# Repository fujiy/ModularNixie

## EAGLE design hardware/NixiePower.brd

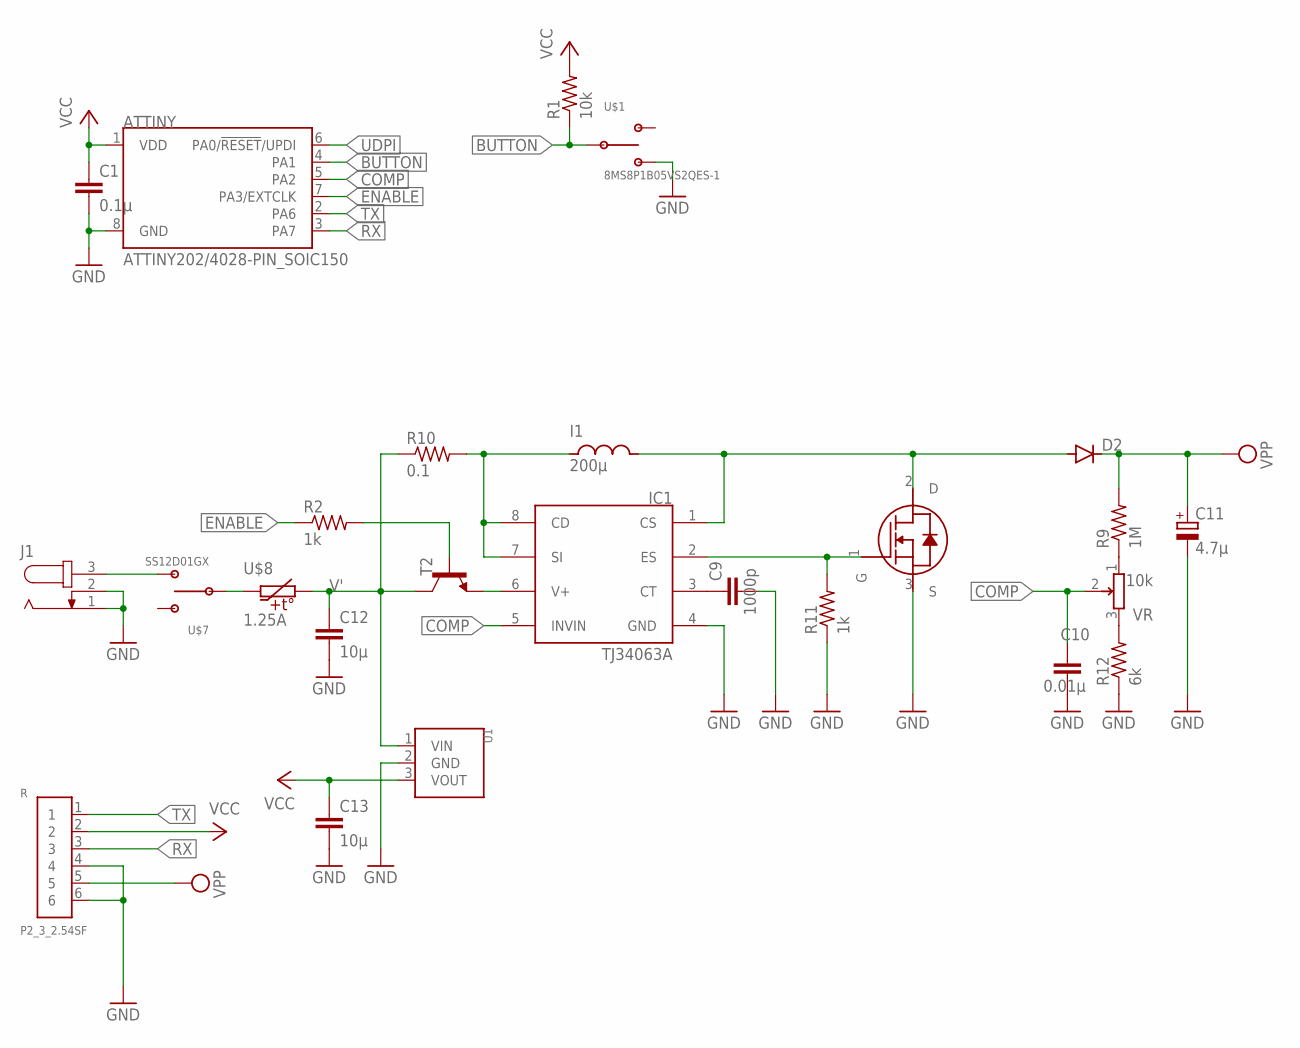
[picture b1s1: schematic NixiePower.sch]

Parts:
ATTINY: ATTINY202/4028-PIN_SOIC150; SOIC127P600X175-8N
C1: 0.1µ; C0603
C9: 1000p; C0603
C10: 0.01µ; C0603
C11: 4.7µ; E5-10,5
C12, C13: 10µ; C0603
D2: DIODE-DO15-12; DO15-12
I1: 200µ; NR10050
IC1: TJ34063A; SOP8
J1: JACK-PLUG1; SPC4078
R: P2_3_2.54SF
R1: 10k; R0603
R2, R11: 1k; R0603
R9: 1M; R0603
R10: 0.1; R0603
R12: 6k; R0603
T1: R6006AND; CPT3
T2: -NPN-SOT23-EBC; SOT23-EBC
U1: VX078XX-500
U$1: 8MS8P1B05VS2QES-1
U$7: SS12D01GX
U$8: 1.25A; SMD1812P
VR: 10k; RK09D

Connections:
BUTTON: ATTINY.4 (PA1), R1.1, U$1.2 (C)
COMP: ATTINY.5 (PA2), C10.1, IC1.5 (INVIN), VR.2
ENABLE: ATTINY.7 (PA3/EXTCLK), R2.1
GND: ATTINY.8 (GND), C1.2, C9.2, C10.2, C11.-, C12.2, C13.2, IC1.4 (GND), J1.1, J1.2, R.4, R.6, R11.1, R12.1, T1.3 (S), U1.2 (GND), U$1.3 (B)
unnamed: IC1.6 (V+), T2.E
unnamed: R2.2, T2.B
unnamed: U$7.2 (C), U$8.1
unnamed: J1.3, U$7.3 (B)
unnamed: D2.A, I1.2, IC1.1 (CS), T1.2 (D)
unnamed: C9.1, IC1.3 (CT)
unnamed: I1.1, IC1.7 (SI), IC1.8 (CD), R10.2
unnamed: IC1.2 (ES), R11.2, T1.1 (G)
unnamed: R9.1, VR.1 (3)
unnamed: R12.2, VR.3 (1)
RX: ATTINY.3 (PA7), R.3
TX: ATTINY.2 (PA6), R.1
UDPI: ATTINY.6 (PA0/!RESET!/UPDI)
V': C12.1, R10.1, T2.C, U1.1 (VIN), U$8.2
VCC: ATTINY.1 (VDD), C1.1, C13.1, R.2, R1.2, U1.3 (VOUT)
VPP: C11.+, D2.C, R.5, R9.2

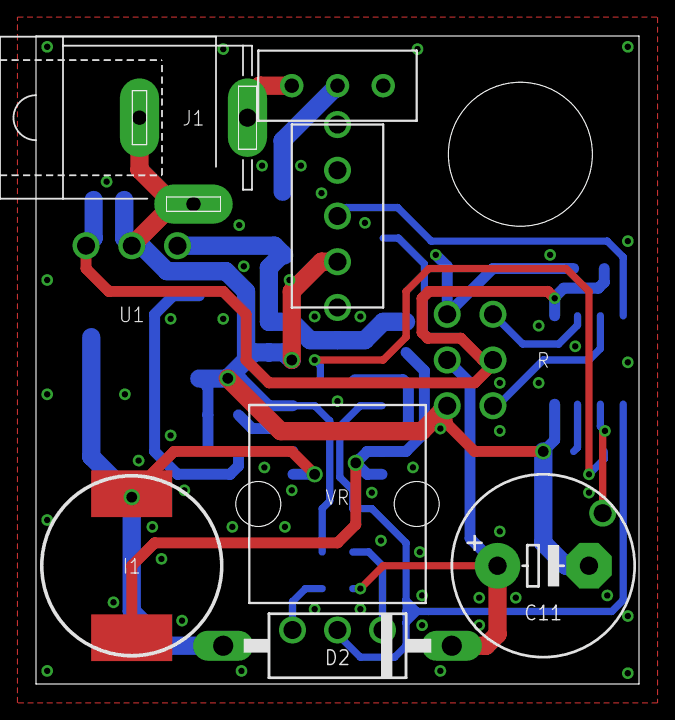
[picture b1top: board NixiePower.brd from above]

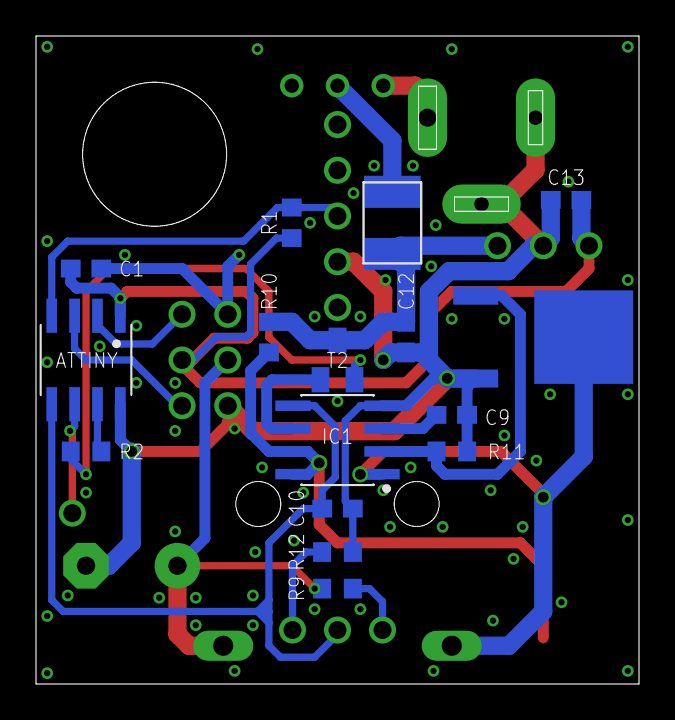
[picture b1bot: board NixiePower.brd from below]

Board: 2 copper layers, 33.5 x 36.0 mm, 25 parts (16 on the bottom side), 19 nets.

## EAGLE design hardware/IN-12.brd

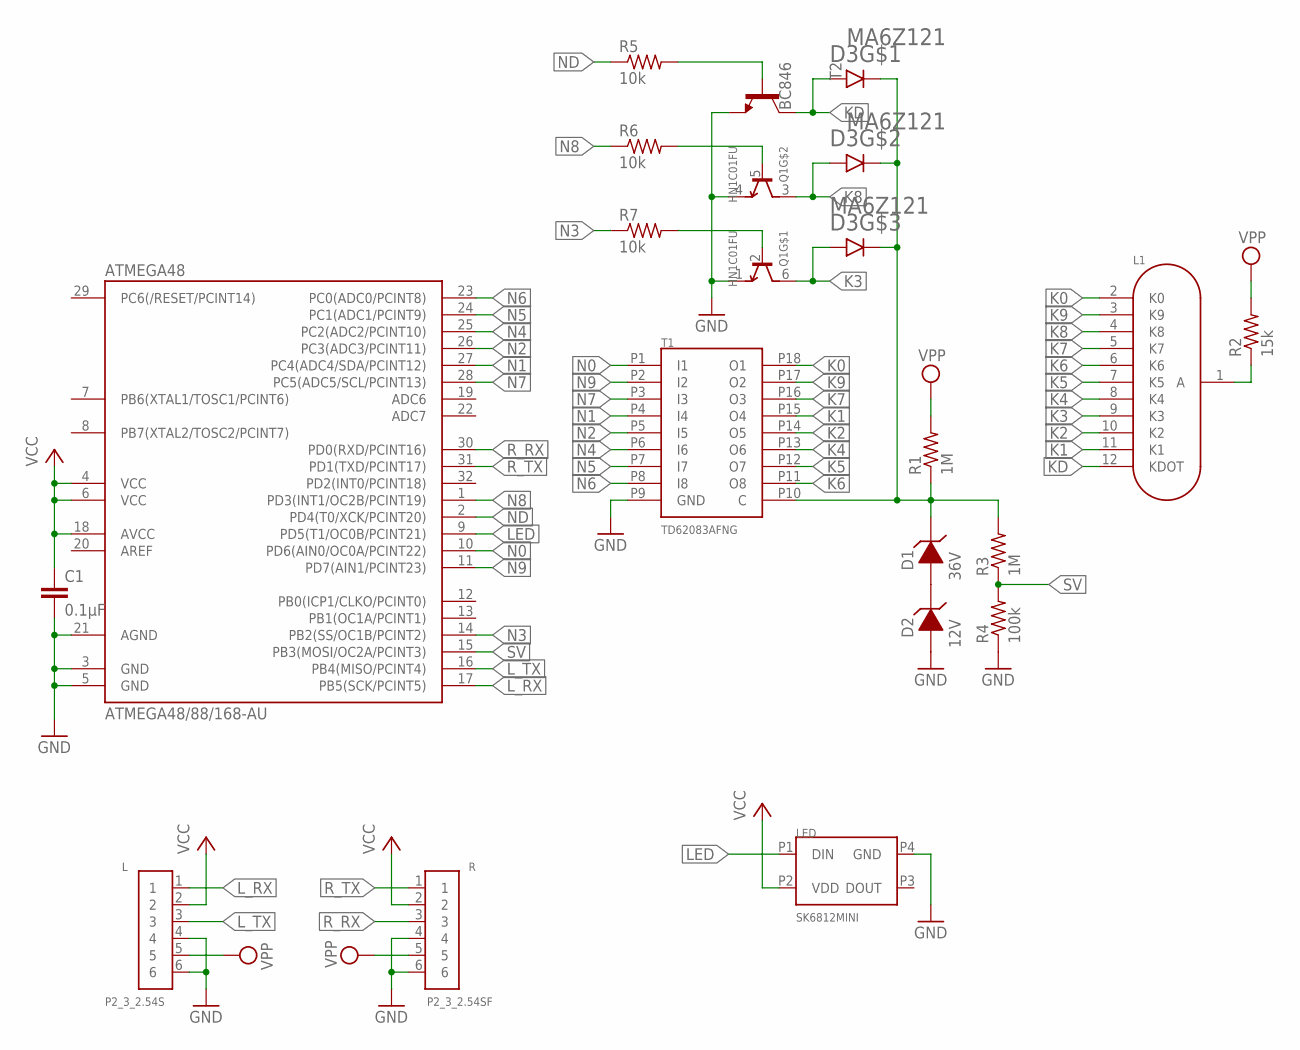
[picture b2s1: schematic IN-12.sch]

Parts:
ATMEGA48: ATMEGA48/88/168-AU; TQFP32-08
C1: 0.1µF; C0603
D1: 36V; S-MINI-2P
D2: 12V; S-MINI-2P
D3: MA6Z121; SMINI6-F1
L: P2_3_2.54S
L1: IN-12B_PS; IN-12_PS
LED: SK6812MINI; SK68XXMINI
Q1: HN1C01FU; SOT-363
R: P2_3_2.54SF
R1, R3: 1M; R0603
R2: 15k; R1206
R4: 100k; R0603
R5, R6, R7: 10k; R0603
T1: TD62083AFNG; SSOP18-P-225-0.65
T2: BC846; SOT23

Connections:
GND: ATMEGA48.3 (GND), ATMEGA48.5 (GND), ATMEGA48.21 (AGND), C1.2, D2.1 (A), L.4, L.6, LED.P4 (GND), Q1.1 (E), Q1.4 (E), R.4, R.6, R4.1, T1.P9 (GND), T2.2 (E)
K0: L1.2 (K0), T1.P18 (O1)
K1: L1.11 (K1), T1.P15 (O4)
K2: L1.10 (K2), T1.P14 (O5)
K3: D3.P3 (A), L1.9 (K3), Q1.6 (C)
K4: L1.8 (K4), T1.P13 (O6)
K5: L1.7 (K5), T1.P12 (O7)
K6: L1.6 (K6), T1.P11 (O8)
K7: L1.5 (K7), T1.P16 (O3)
K8: D3.P2 (A), L1.4 (K8), Q1.3 (C)
K9: L1.3 (K9), T1.P17 (O2)
KD: D3.P1 (A), L1.12 (KDOT), T2.3 (C)
LED: ATMEGA48.9 (PD5(T1/OC0B/PCINT21)), LED.P1 (DIN)
L_RX: ATMEGA48.17 (PB5(SCK/PCINT5)), L.1
L_TX: ATMEGA48.16 (PB4(MISO/PCINT4)), L.3
N0: ATMEGA48.10 (PD6(AIN0/OC0A/PCINT22)), T1.P1 (I1)
N1: ATMEGA48.27 (PC4(ADC4/SDA/PCINT12)), T1.P4 (I4)
N2: ATMEGA48.26 (PC3(ADC3/PCINT11)), T1.P5 (I5)
N3: ATMEGA48.14 (PB2(SS/OC1B/PCINT2)), R7.1
N4: ATMEGA48.25 (PC2(ADC2/PCINT10)), T1.P6 (I6)
N5: ATMEGA48.24 (PC1(ADC1/PCINT9)), T1.P7 (I7)
N6: ATMEGA48.23 (PC0(ADC0/PCINT8)), T1.P8 (I8)
N7: ATMEGA48.28 (PC5(ADC5/SCL/PCINT13)), T1.P3 (I3)
N8: ATMEGA48.1 (PD3(INT1/OC2B/PCINT19)), R6.1
N9: ATMEGA48.11 (PD7(AIN1/PCINT23)), T1.P2 (I2)
unnamed: D1.1 (A), D2.2 (C)
unnamed: D1.2 (C), D3.P4 (C), D3.P5 (C), D3.P6 (C), R1.1, R3.2, T1.P10 (C)
unnamed: L1.1 (A), R2.1
unnamed: Q1.2 (B), R7.2
unnamed: Q1.5 (B), R6.2
unnamed: R5.2, T2.1 (B)
ND: ATMEGA48.2 (PD4(T0/XCK/PCINT20)), R5.1
R_RX: ATMEGA48.30 (PD0(RXD/PCINT16)), R.3
R_TX: ATMEGA48.31 (PD1(TXD/PCINT17)), R.1
SV: ATMEGA48.15 (PB3(MOSI/OC2A/PCINT3)), R3.1, R4.2
VCC: ATMEGA48.4 (VCC), ATMEGA48.6 (VCC), ATMEGA48.18 (AVCC), C1.1, L.2, LED.P2 (VDD), R.2
VPP: L.5, R.5, R1.2, R2.2

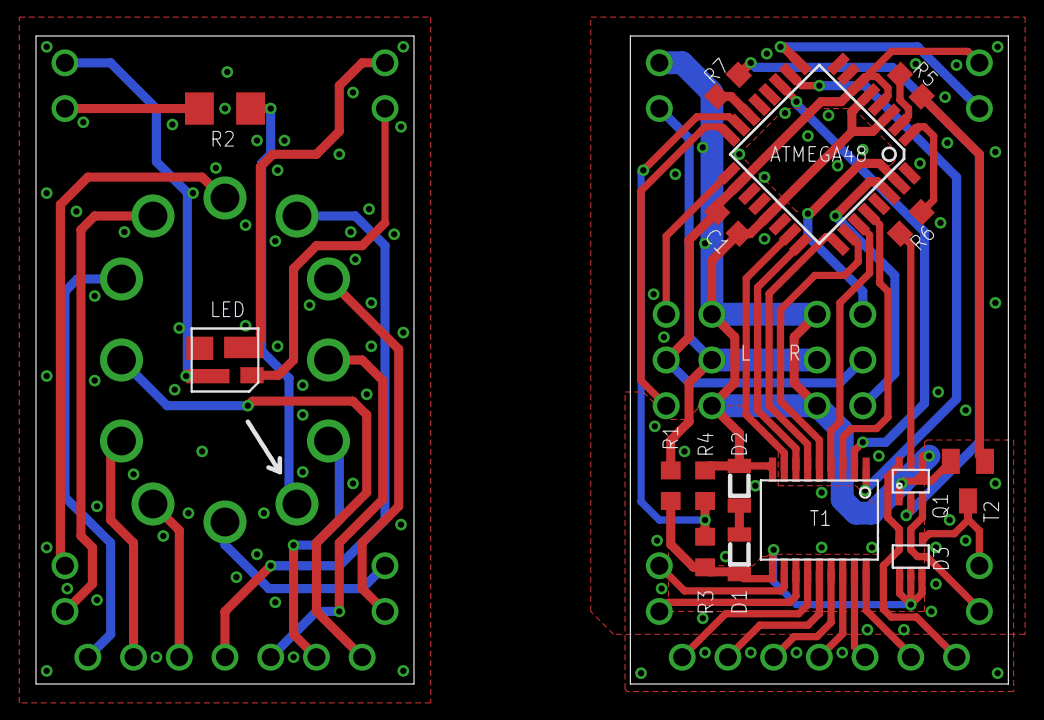
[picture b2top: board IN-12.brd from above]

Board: 2 copper layers, 21.0 x 36.0 mm, 19 parts (1 on the bottom side), 37 nets.

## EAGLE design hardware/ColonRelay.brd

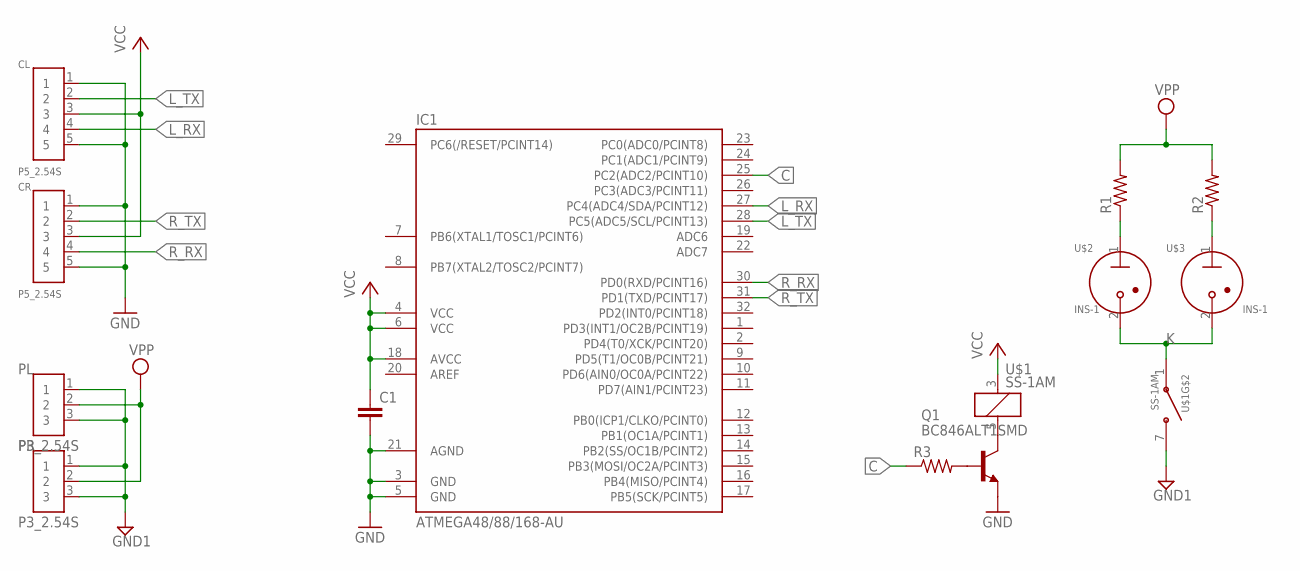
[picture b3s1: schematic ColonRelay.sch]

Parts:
C1: C-EUC0603K; C0603K
CL: P5_2.54S
CR: P5_2.54S
IC1: ATMEGA48/88/168-AU; TQFP32-08
PL: P3_2.54S
PR: P3_2.54S
Q1: BC846ALT1SMD; SOT23
R1, R2: R-US_R1206; R1206
R3: R-US_R0603; R0603
U$1: SS-1AM; SS-1****M
U$2, U$3: INS-1

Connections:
C: IC1.25 (PC2(ADC2/PCINT10)), R3.1
GND: C1.2, CL.1, CL.5, CR.1, CR.5, IC1.3 (GND), IC1.5 (GND), IC1.21 (AGND), Q1.2 (E)
GND1: PL.1, PL.3, PR.1, PR.3, U$1.7
K: U$1.1, U$2.2 (C), U$3.2 (C)
L_RX: CL.4, IC1.27 (PC4(ADC4/SDA/PCINT12))
L_TX: CL.2, IC1.28 (PC5(ADC5/SCL/PCINT13))
unnamed: Q1.3 (C), U$1.5 (2)
unnamed: R2.1, U$3.1 (A)
unnamed: R1.1, U$2.1 (A)
unnamed: Q1.1 (B), R3.2
R_RX: CR.4, IC1.30 (PD0(RXD/PCINT16))
R_TX: CR.2, IC1.31 (PD1(TXD/PCINT17))
VCC: C1.1, CL.3, CR.3, IC1.4 (VCC), IC1.6 (VCC), IC1.18 (AVCC), U$1.3 (1)
VPP: PL.2, PR.2, R1.2, R2.2

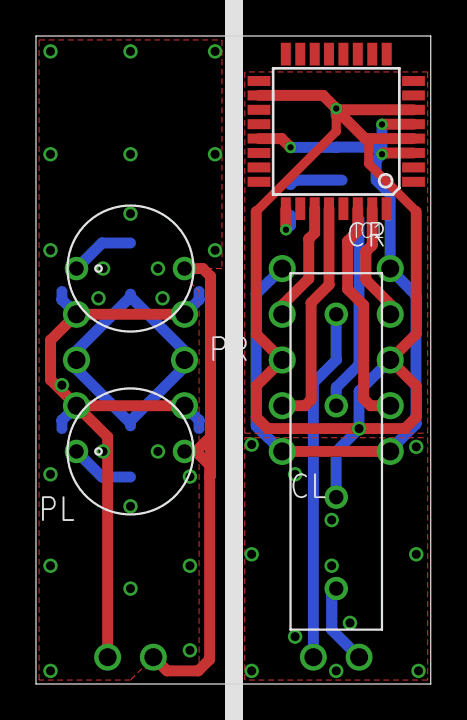
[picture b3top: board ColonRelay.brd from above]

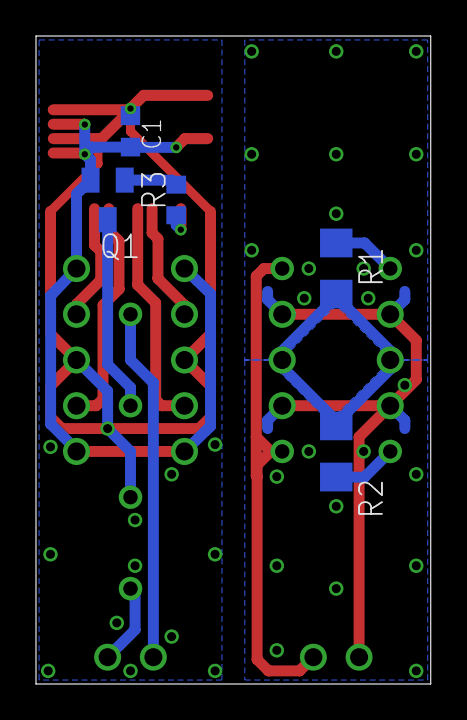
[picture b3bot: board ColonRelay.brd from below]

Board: 2 copper layers, 21.9 x 36.0 mm, 13 parts (5 on the bottom side), 14 nets.

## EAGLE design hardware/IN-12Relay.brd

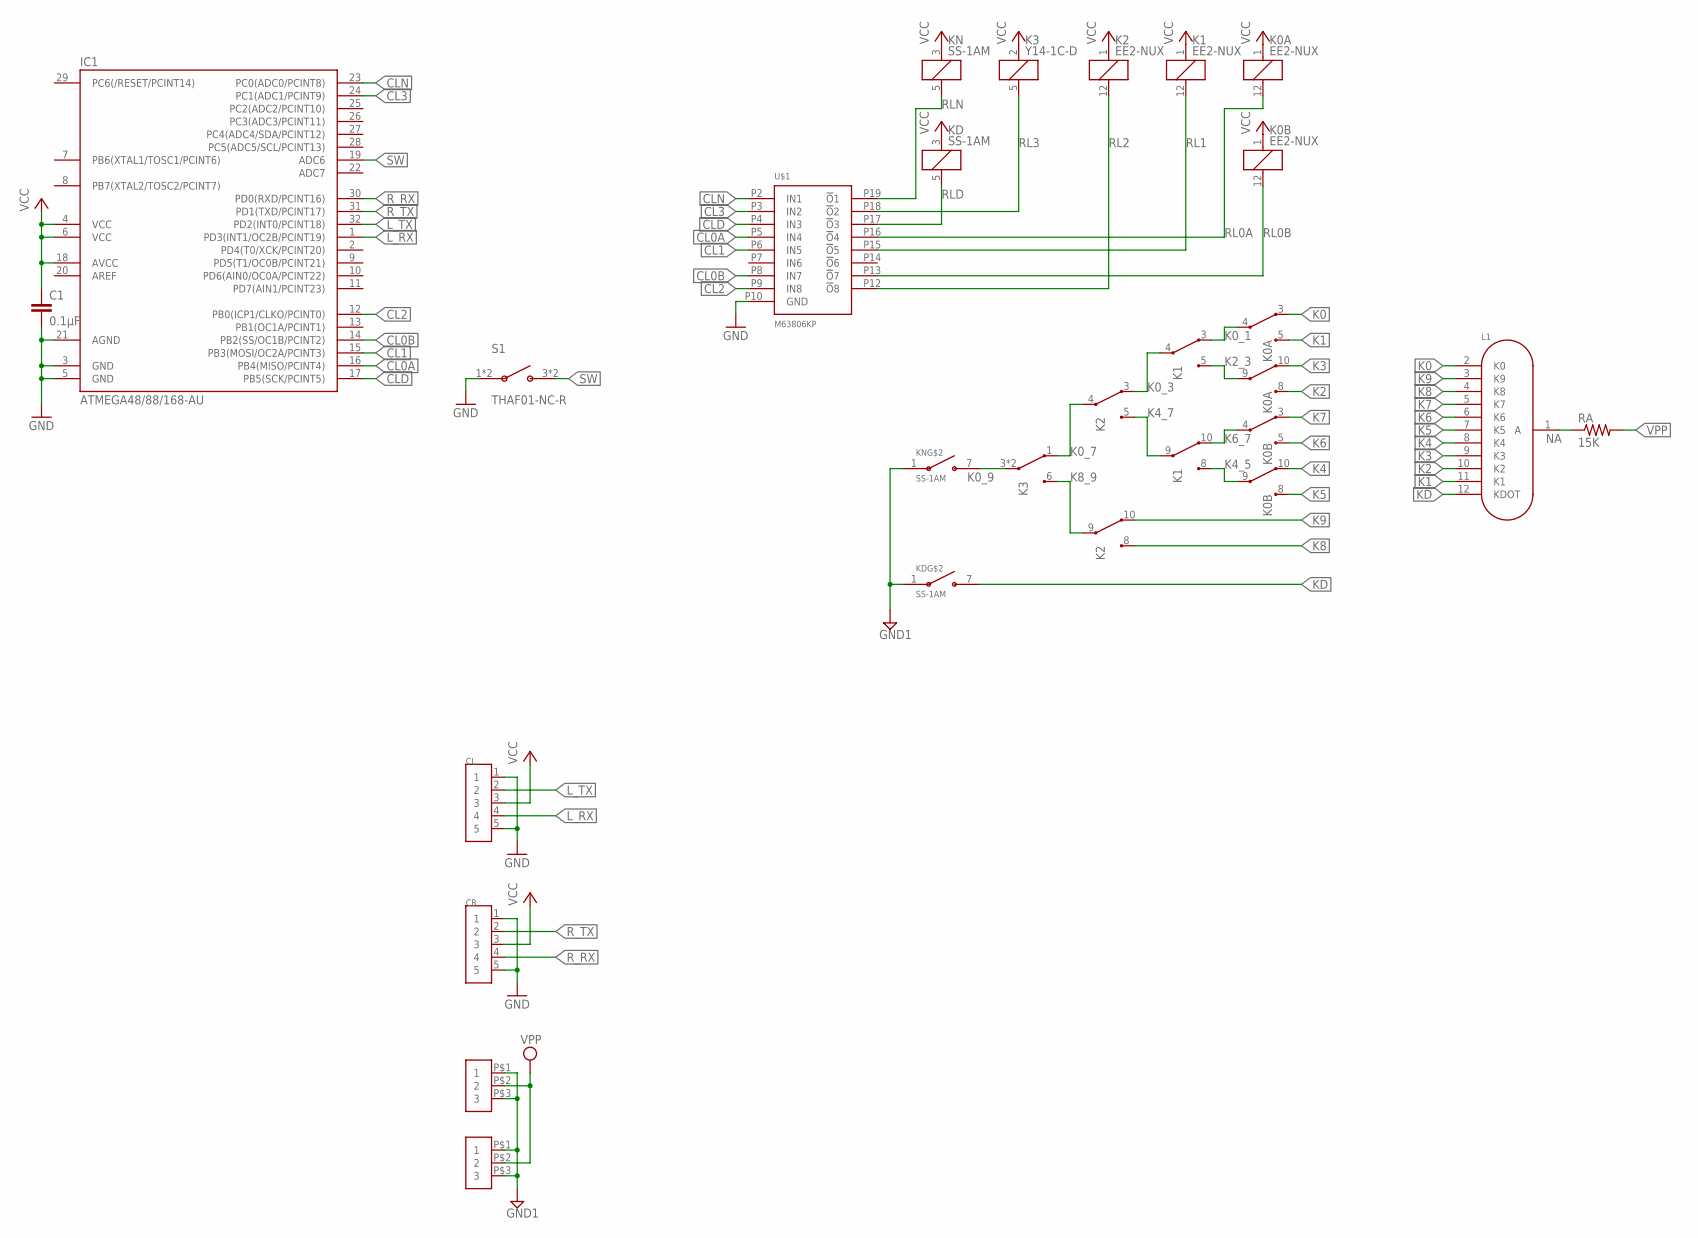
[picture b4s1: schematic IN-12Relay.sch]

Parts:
C1: 0.1µF; C0603K
CL: P5; P5_2.54
CR: P5; P5_2.54
IC1: ATMEGA48/88/168-AU; TQFP32-08
K0A, K0B, K1, K2: EE2-NUX; EE2-*NUX
K3: Y14-1C-D; Y14*-1C-*D*
KD: SS-1AM; SS-1****M
KN: SS-1AM; SS-1****M
L1: IN-12B_PS; IN-12_PS
PL: P3; P3_2.54
PR: P3; P3_2.54
RA: 15K; R1206
S1: THAF01-NC-R
U$1: M63806KP; 20P2E

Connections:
CL0A: IC1.16 (PB4(MISO/PCINT4)), U$1.P5 (IN4)
CL0B: IC1.14 (PB2(SS/OC1B/PCINT2)), U$1.P8 (IN7)
CL1: IC1.15 (PB3(MOSI/OC2A/PCINT3)), U$1.P6 (IN5)
CL2: IC1.12 (PB0(ICP1/CLKO/PCINT0)), U$1.P9 (IN8)
CL3: IC1.24 (PC1(ADC1/PCINT9)), U$1.P3 (IN2)
CLD: IC1.17 (PB5(SCK/PCINT5)), U$1.P4 (IN3)
CLN: IC1.23 (PC0(ADC0/PCINT8)), U$1.P2 (IN1)
GND: C1.2, CL.1, CL.5, CR.1, CR.5, IC1.3 (GND), IC1.5 (GND), IC1.21 (AGND), S1.1 (A), S1.2 (A), U$1.P10 (GND)
GND1: KD.1, KN.1, PL.P$1 (1), PL.P$3 (3), PR.P$1 (1), PR.P$3 (3)
K0: K0A.3 (S), L1.2 (K0)
K0_1: K0A.4, K1.3 (S)
K0_3: K1.4, K2.3 (S)
K0_7: K2.4, K3.1 (S)
K0_9: K3.3, K3.4, KN.7
K1: K0A.5 (O), L1.11 (K1)
K2: K0A.8 (O), L1.10 (K2)
K2_3: K0A.9, K1.5 (O)
K3: K0A.10 (S), L1.9 (K3)
K4: K0B.10 (S), L1.8 (K4)
K4_5: K0B.9, K1.8 (O)
K4_7: K1.9, K2.5 (O)
K5: K0B.8 (O), L1.7 (K5)
K6: K0B.5 (O), L1.6 (K6)
K6_7: K0B.4, K1.10 (S)
K7: K0B.3 (S), L1.5 (K7)
K8: K2.8 (O), L1.4 (K8)
K8_9: K2.9, K3.6 (O)
K9: K2.10 (S), L1.3 (K9)
KD: KD.7, L1.12 (KDOT)
L_RX: CL.4, IC1.1 (PD3(INT1/OC2B/PCINT19))
L_TX: CL.2, IC1.32 (PD2(INT0/PCINT18))
NA: L1.1 (A), RA.1
RL0A: K0A.12 (2), U$1.P16 (!O!4)
RL0B: K0B.12 (2), U$1.P13 (!O!7)
RL1: K1.12 (2), U$1.P15 (!O!5)
RL2: K2.12 (2), U$1.P12 (!O!8)
RL3: K3.5 (2), U$1.P18 (!O!2)
RLD: KD.5 (2), U$1.P17 (!O!3)
RLN: KN.5 (2), U$1.P19 (!O!1)
R_RX: CR.4, IC1.30 (PD0(RXD/PCINT16))
R_TX: CR.2, IC1.31 (PD1(TXD/PCINT17))
SW: IC1.19 (ADC6), S1.3 (B), S1.4 (B)
VCC: C1.1, CL.3, CR.3, IC1.4 (VCC), IC1.6 (VCC), IC1.18 (AVCC), K0A.1, K0B.1, K1.1, K2.1, K3.2 (1), KD.3 (1), KN.3 (1)
VPP: PL.P$2 (2), PR.P$2 (2), RA.2

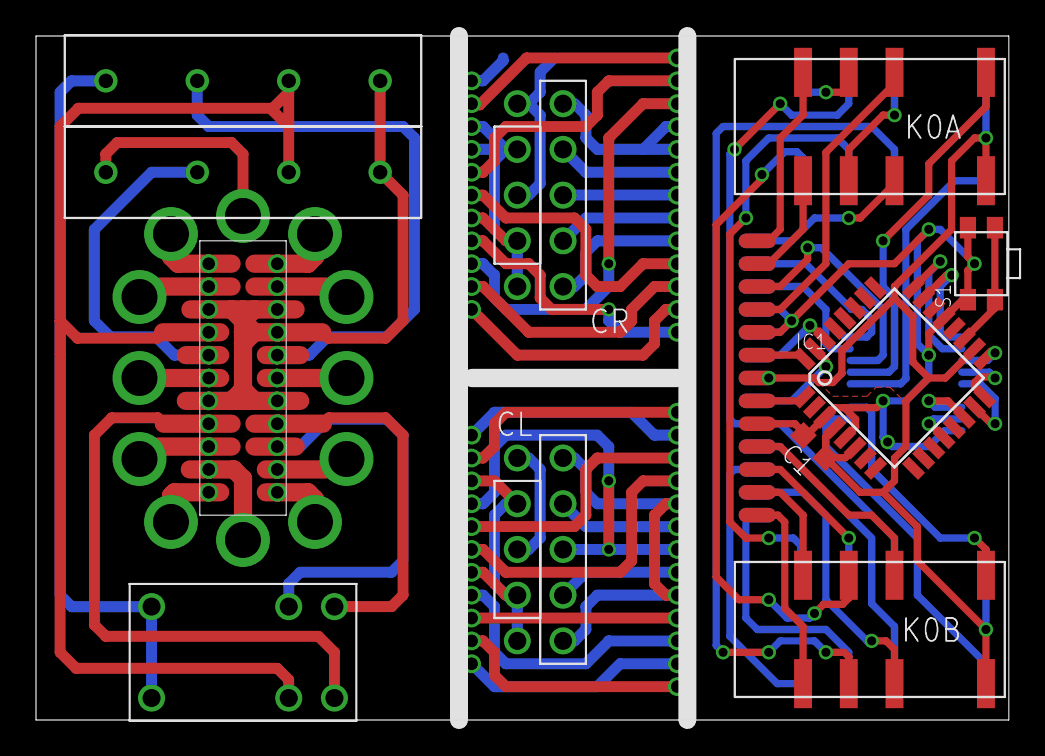
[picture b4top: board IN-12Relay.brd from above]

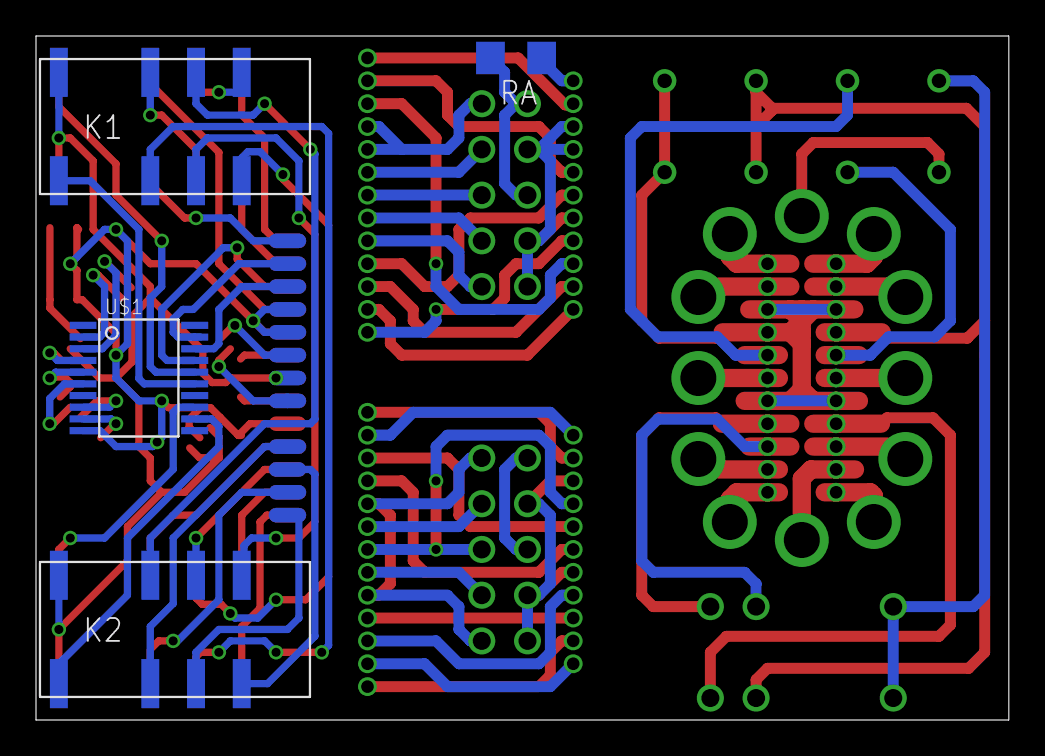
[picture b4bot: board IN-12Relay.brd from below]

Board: 2 copper layers, 54.0 x 38.0 mm, 17 parts (4 on the bottom side), 44 nets.

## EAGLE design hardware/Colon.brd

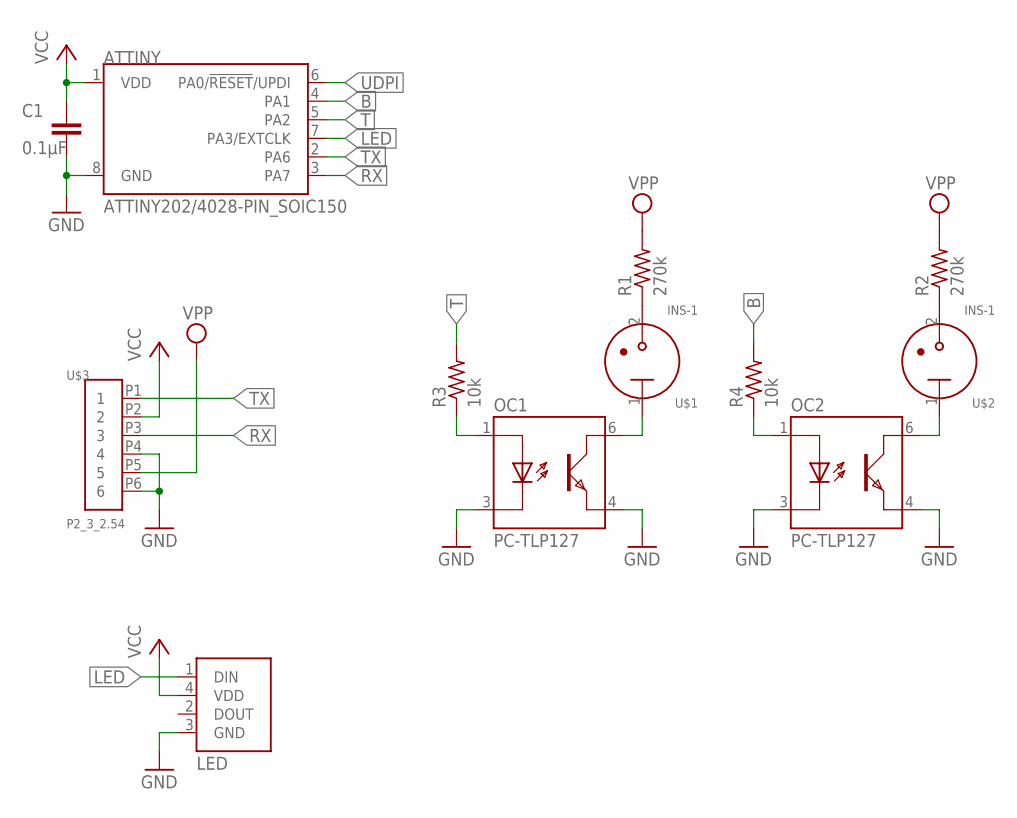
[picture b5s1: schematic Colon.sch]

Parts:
ATTINY: ATTINY202/4028-PIN_SOIC150; SOIC127P600X175-8N
C1: 0.1µF; C0603
LED: SK6812SIDE
OC1, OC2: PC-TLP127; MINIFLAT4
R1, R2: 270k; R0603
R3, R4: 10k; R0603
U$1, U$2: INS-1
U$3: P2_3_2.54

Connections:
B: ATTINY.4 (PA1), R4.2
GND: ATTINY.8 (GND), C1.2, LED.3 (GND), OC1.3 (C), OC1.4 (TE), OC2.3 (C), OC2.4 (TE), U$3.P4 (4), U$3.P6 (6)
LED: ATTINY.7 (PA3/EXTCLK), LED.1 (DIN)
unnamed: R1.1, U$1.2 (C)
unnamed: R2.1, U$2.2 (C)
unnamed: OC1.6 (TC), U$1.1 (A)
unnamed: OC2.6 (TC), U$2.1 (A)
unnamed: OC2.1 (A), R4.1
unnamed: OC1.1 (A), R3.1
RX: ATTINY.3 (PA7), U$3.P3 (3)
T: ATTINY.5 (PA2), R3.2
TX: ATTINY.2 (PA6), U$3.P1 (1)
UDPI: ATTINY.6 (PA0/!RESET!/UPDI)
VCC: ATTINY.1 (VDD), C1.1, LED.4 (VDD), U$3.P2 (2)
VPP: R1.2, R2.2, U$3.P5 (5)

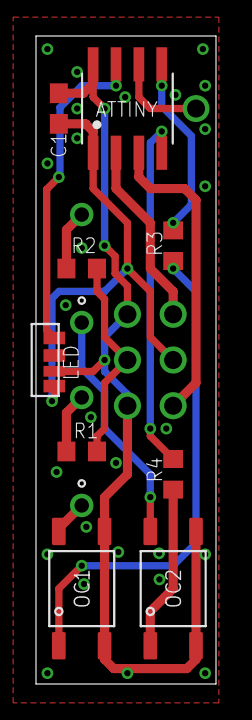
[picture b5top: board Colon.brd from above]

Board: 2 copper layers, 10.0 x 36.0 mm, 12 parts (1 on the bottom side), 14 nets.

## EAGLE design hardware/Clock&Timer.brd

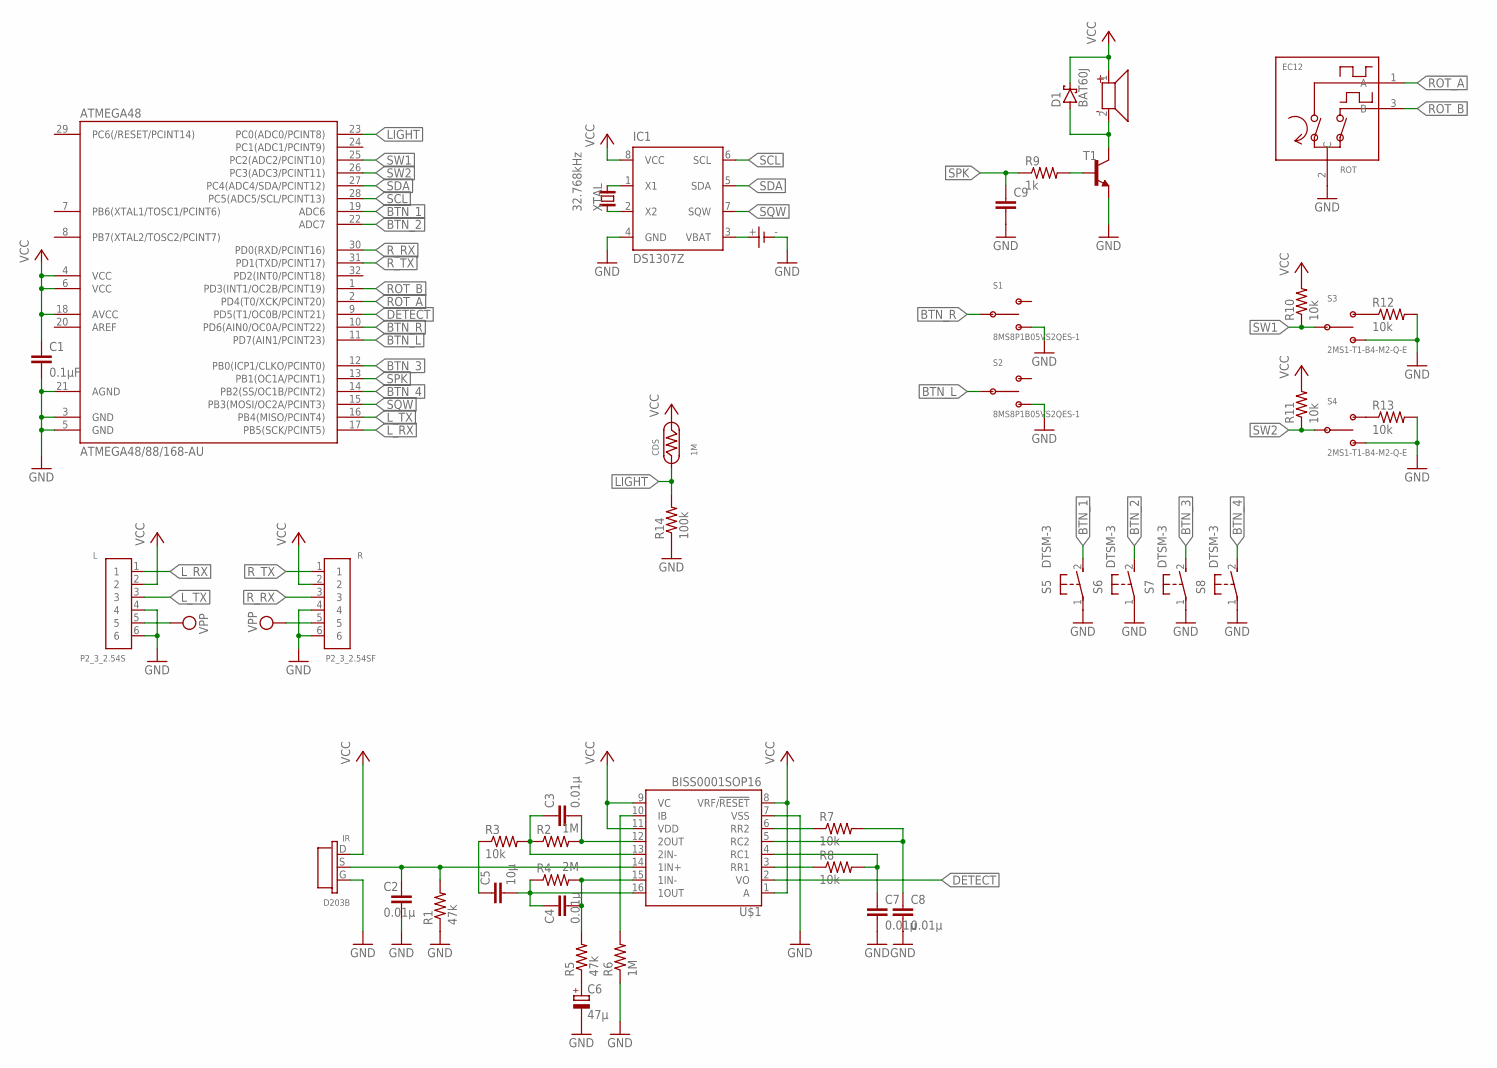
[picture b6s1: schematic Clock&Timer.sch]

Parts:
ATMEGA48: ATMEGA48/88/168-AU; TQFP32-08
BAT: BC1/3N
C1: 0.1µF; C0603
C2, C3, C4, C7, C8: 0.01µ; C0603
C5: 10µ; C0603
C6: 47µ; 153CLV-0605
C9: C-EUC0603; C0603
CDS: 1M; GL55
D1: BAT60J; SOD323_ST
IC1: DS1307Z; SOIC8
IR: D203B
L: P2_3_2.54S
R: P2_3_2.54SF
R1, R5: 47k; R0603
R2, R6: 1M; R0603
R3, R7, R8, R10, R11, R12, R13: 10k; R0603
R4: 2M; R0603
R9: 1k; R0603
R14: 100k; R0603
ROT: EC12
S1, S2: 8MS8P1B05VS2QES-1
S3, S4: 2MS1-T1-B4-M2-Q-E
S5, S6, S7, S8: DTSM-3
T1: -NPN-SOT23-EBC; SOT23-EBC
U$1: BISS0001SOP16; SOP16
U$9: UGCM0903EPD
XTAL: 32.768kHz; FC-255

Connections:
BTN_1: ATMEGA48.19 (ADC6), S5.2
BTN_2: ATMEGA48.22 (ADC7), S6.2
BTN_3: ATMEGA48.12 (PB0(ICP1/CLKO/PCINT0)), S7.2
BTN_4: ATMEGA48.14 (PB2(SS/OC1B/PCINT2)), S8.2
BTN_L: ATMEGA48.11 (PD7(AIN1/PCINT23)), S2.2 (C)
BTN_R: ATMEGA48.10 (PD6(AIN0/OC0A/PCINT22)), S1.2 (C)
DETECT: ATMEGA48.9 (PD5(T1/OC0B/PCINT21)), U$1.2 (VO)
GND: ATMEGA48.3 (GND), ATMEGA48.5 (GND), ATMEGA48.21 (AGND), BAT.- (V-), C1.2, C2.2, C6.-, C7.2, C8.2, C9.2, IC1.4 (GND), IR.G (GND), L.4, L.6, R.4, R.6, R1.1, R6.1, R12.2, R13.2, R14.1, ROT.2 (C), S1.3 (B), S2.3 (B), S3.3 (B), S4.3 (B), S5.1, S6.1, S7.1, S8.1, T1.E, U$1.7 (VSS)
LIGHT: ATMEGA48.23 (PC0(ADC0/PCINT8)), CDS.1, R14.2
L_RX: ATMEGA48.17 (PB5(SCK/PCINT5)), L.1
L_TX: ATMEGA48.16 (PB4(MISO/PCINT4)), L.3
unnamed: C2.1, IR.S (OUTPUT), R1.2, U$1.14 (1IN+)
unnamed: C3.2, R2.2, U$1.12 (2OUT)
unnamed: C3.1, R2.1, R3.2, U$1.13 (2IN-)
unnamed: C4.2, R4.2, R5.2, U$1.15 (1IN-)
unnamed: C5.1, R3.1
unnamed: C4.1, C5.2, R4.1, U$1.16 (1OUT)
unnamed: C6.+, R5.1
unnamed: R6.2, U$1.10 (IB)
unnamed: R7.1, U$1.6 (RR2)
unnamed: C8.1, R7.2, U$1.5 (RC2)
unnamed: IC1.1 (X1), XTAL.2
unnamed: R8.1, U$1.3 (RR1)
unnamed: C7.1, R8.2, U$1.4 (RC1)
unnamed: D1.A, T1.C, U$9.2
unnamed: R9.2, T1.B
unnamed: IC1.2 (X2), XTAL.1
unnamed: R12.1, S3.1 (A)
unnamed: R13.1, S4.1 (A)
ROT_A: ATMEGA48.2 (PD4(T0/XCK/PCINT20)), ROT.1 (A)
ROT_B: ATMEGA48.1 (PD3(INT1/OC2B/PCINT19)), ROT.3 (B)
R_RX: ATMEGA48.30 (PD0(RXD/PCINT16)), R.3
R_TX: ATMEGA48.31 (PD1(TXD/PCINT17)), R.1
SCL: ATMEGA48.28 (PC5(ADC5/SCL/PCINT13)), IC1.6 (SCL)
SDA: ATMEGA48.27 (PC4(ADC4/SDA/PCINT12)), IC1.5 (SDA)
SPK: ATMEGA48.13 (PB1(OC1A/PCINT1)), C9.1, R9.1
SQW: ATMEGA48.15 (PB3(MOSI/OC2A/PCINT3)), IC1.7 (SQW)
SW1: ATMEGA48.25 (PC2(ADC2/PCINT10)), R10.1, S3.2 (C)
SW2: ATMEGA48.26 (PC3(ADC3/PCINT11)), R11.1, S4.2 (C)
VBAT: BAT.+ (V+), IC1.3 (VBAT)
VCC: ATMEGA48.4 (VCC), ATMEGA48.6 (VCC), ATMEGA48.18 (AVCC), C1.1, CDS.2, D1.C, IC1.8 (VCC), IR.D (VIN), L.2, R.2, R10.2, R11.2, U$1.1 (A), U$1.8 (VRF/!RESET!), U$1.9 (VC), U$1.11 (VDD), U$9.1
VPP: L.5, R.5

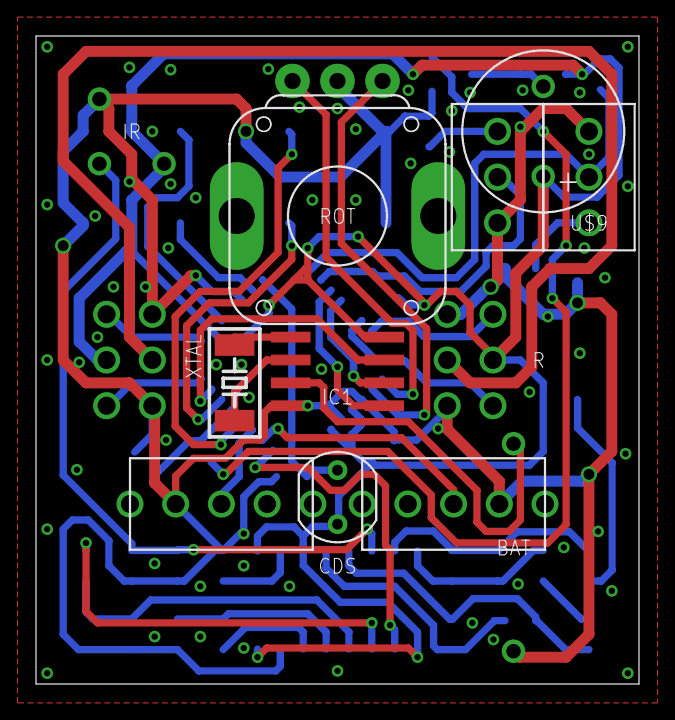
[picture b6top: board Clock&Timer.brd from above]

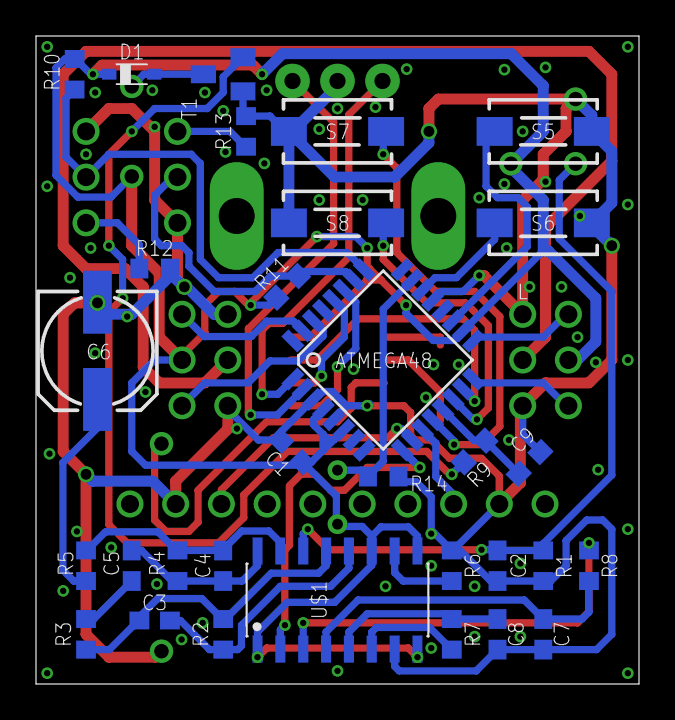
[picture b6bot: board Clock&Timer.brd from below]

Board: 2 copper layers, 33.5 x 36.0 mm, 44 parts (32 on the bottom side), 42 nets.

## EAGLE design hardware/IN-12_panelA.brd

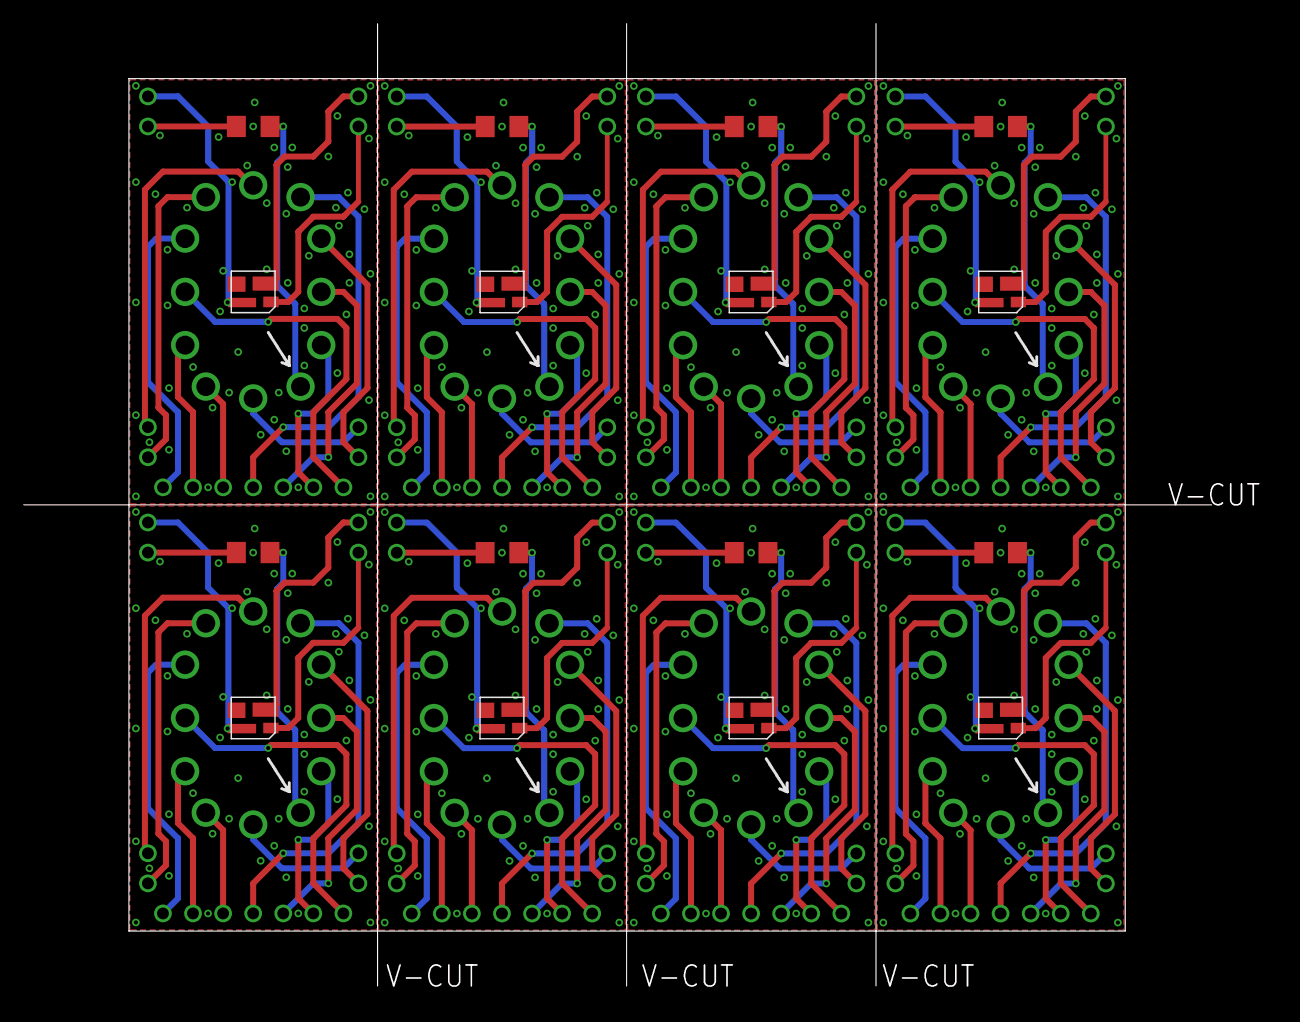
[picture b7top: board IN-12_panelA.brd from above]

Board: 2 copper layers, 100.3 x 81.3 mm, 24 parts (0 on the bottom side), 8 nets.

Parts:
L1, L2, L3, L4, L5, L6, L7, L8: IN-12B_PS; IN-12_PS
LED, LED1, LED2, LED3, LED4, LED5, LED6, LED7: SK6812MINI; SK68XXMINI
R1, R2, R3, R4, R5, R6, R7, R8: 15k; R1206

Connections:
unnamed: L2.1, R1.1
unnamed: L3.1, R3.1
unnamed: L4.1, R4.1
unnamed: L5.1, R5.1
unnamed: L6.1, R6.1
unnamed: L7.1, R7.1
unnamed: L8.1, R8.1
unnamed: L1.1, R2.1

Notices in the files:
parts and their libraries:
m-pad-2.1: License : GNU General Public License version 2 (see bottom)
